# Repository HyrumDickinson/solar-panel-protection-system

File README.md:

# Solar Panel Protection System

## Project overview
This code represents the software portion of an ongoing effort to build a tool that monitors solar energy systems and keeps panels from overheating.

This project is funded by the University of Illinois Department of Electrical & Computer Engineering and is based out of the Center for Electric Machinery & Electromechanics. The project lies under the direction of Arijit Banerjee, Assistant Professor in ECE. The software portion of the project is undergoing construction by undergraduate student workers Hyrum Dickinson and Benjamin Olaivar, supervised by Kevin Colravy, Research Engineer at CEME. Only the software portion of the solar panel protection system project is hosted on this repo.

The original solar panel protection system was created by then-undergraduate students Dillon Vadgama, Douglas Lee, and Sachin Reddy for their fall 2019 senior design project. Dubbed "Smart Interface for ECEB Research Solar Panels," the project won the Texas Instruments Best Project Award. Now, researchers from the University of Illinois are attempting to improve on their prototype to create a robust, scalable tool that can monitor entire solar energy systems and reliably keep individual panels from overheating.

This branch is primarily focused on the development of the onboard arduino code. This code will encompass everything from ethernet communication to sensor data reading. The majority of work done in this branch will be done under the 'arduino_data' directory, the 'test' files. Files in this directory are organized using platformio, which allows for convenient access/storage of libraries, test code, and other files. 

## Repository setup
### `main`
The latest stable, deployable version of the code is stored in the `main` branch.
### `python-2-version` and `python-3-version`
Until code is fully ported to Python 3, these branches are the `main` branches of the code in their respective language.
### `original`
It is important to note that the original code for this project is not our own. It was written by Dillon Vadgama, Douglas Lee, and Sachin Reddy as part of a senior design project. The exact original code, including the original README, is stored in this branch. 

## System tools  
### Software  
Microprocessor code - Arduino Language  
Original GUI - Python 2 & Tkinter  
New GUI - Processing 3  
README & WRITEME files - Markdown  
### Hardware (not included in repo)  
Arduino Uno with Wifi  
Custom PCB Arduino Shield  

## Old Python GUI
### Dependencies
- matplotlib  
- tkinter (Python 3) or Tkinter (Python 2)  
- sqlite3  
- pillow  
- datetime  
The original code was written to for PIL. PIL is now unsupported - its own website recommends against its use. Pillow is a maintained backwords-compatible fork of PIL.
### Run
run Main.py in your preferred Python environment
### Building
source venv/bin/activate  
python2 Setup.py py2app -A

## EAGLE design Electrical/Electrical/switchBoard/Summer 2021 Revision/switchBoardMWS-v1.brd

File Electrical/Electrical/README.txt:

================================================================================================
GENERAL
================================================================================================

All PCB's were made using EAGLE 9.5.0
All PCB's were ordered through PCBWay.
Latest Gerber files were zipped and uploaded in each project folder.
For the BOM including parts to populate the PCB's, see the Documentation folder on Box.

================================================================================================
PCBWAY ORDER INFORMATION
================================================================================================

Gerber Files: smartInterface.zip
Board Type: Single Pieces
Different Design in Panel: 1
Size: 100 mm x 100 mm
Quantity: 10
Number of Layers: 4
Layer Stack:
 - L1: smartInterface.top
 - L2: smartInterface.ly2
 - L3: smartInterface.ly3
 - L4: smartInterface.bot
Material: FR-4
FR4-TG: TG 150-160
Thickness: 1.6
Min Track/Spacing: 6/6 mil
Min Hole Size: 0.3 mm
Solder Mask: Red
Silkscreen: White
Gold Fingers: No
Surface Finish: HASL with lead
Via Process: Tenting Vias
Finished Copper: 1 oz Cu
Inner Copper: 1 oz

Gerber Files: switchBoard.zip
Board Type: Single Pieces
Different Design in Panel: 1
Size: 25mm x 100mm
Quantity: 10
Number of Layers: 2
Layer Stack:
 - L1: switchBoard.top
 - L2: switchBoard.bot
Material: FR-4
FR4-TG: TG 150-160
Thickness: 1.6
Min Track/Spacing: 6/6 mil
Min Hole Size: 0.3 mm
Solder Mask: Red
Silkscreen: White
Gold Fingers: No
Surface Finish: HASL with lead
Via Process: Tenting Vias
Finished Copper: 1 oz Cu
Inner Copper: 1 oz

================================================================================================
BURNING THE BOOTLOADER - DO THIS BEFORE MOUNTING THE ATMEGA328P ON THE PCB
================================================================================================
To use the firmware that was originally written for the system, the Arduino bootloader should be burned onto the ATmega328P.

Here are resources to burn the bootloader:
https://www.arduino.cc/en/Tutorial/ArduinoToBreadboard
https://www.arduino.cc/en/Main/Standalone

================================================================================================
FLASHING FIRMWARE
================================================================================================
After burning the bootloader into the ATmega328P, the chip can be placed on the PCB.
The PCB was designed so that the microcontroller could be programmed without removing the chip.
Near the Ethernet connector is a 6 pin header that is used for programming.

The system was designed to be flashed with an FTDI Basic Breakout board from Sparkfun Electronics:
https://www.sparkfun.com/products/9716

Connect this FTDI board to the 6 pin header, and connector a USB cable from the FTDI board to your computer.
You can then use the Arduino IDE to flash any desired Arduino firmware to the system.

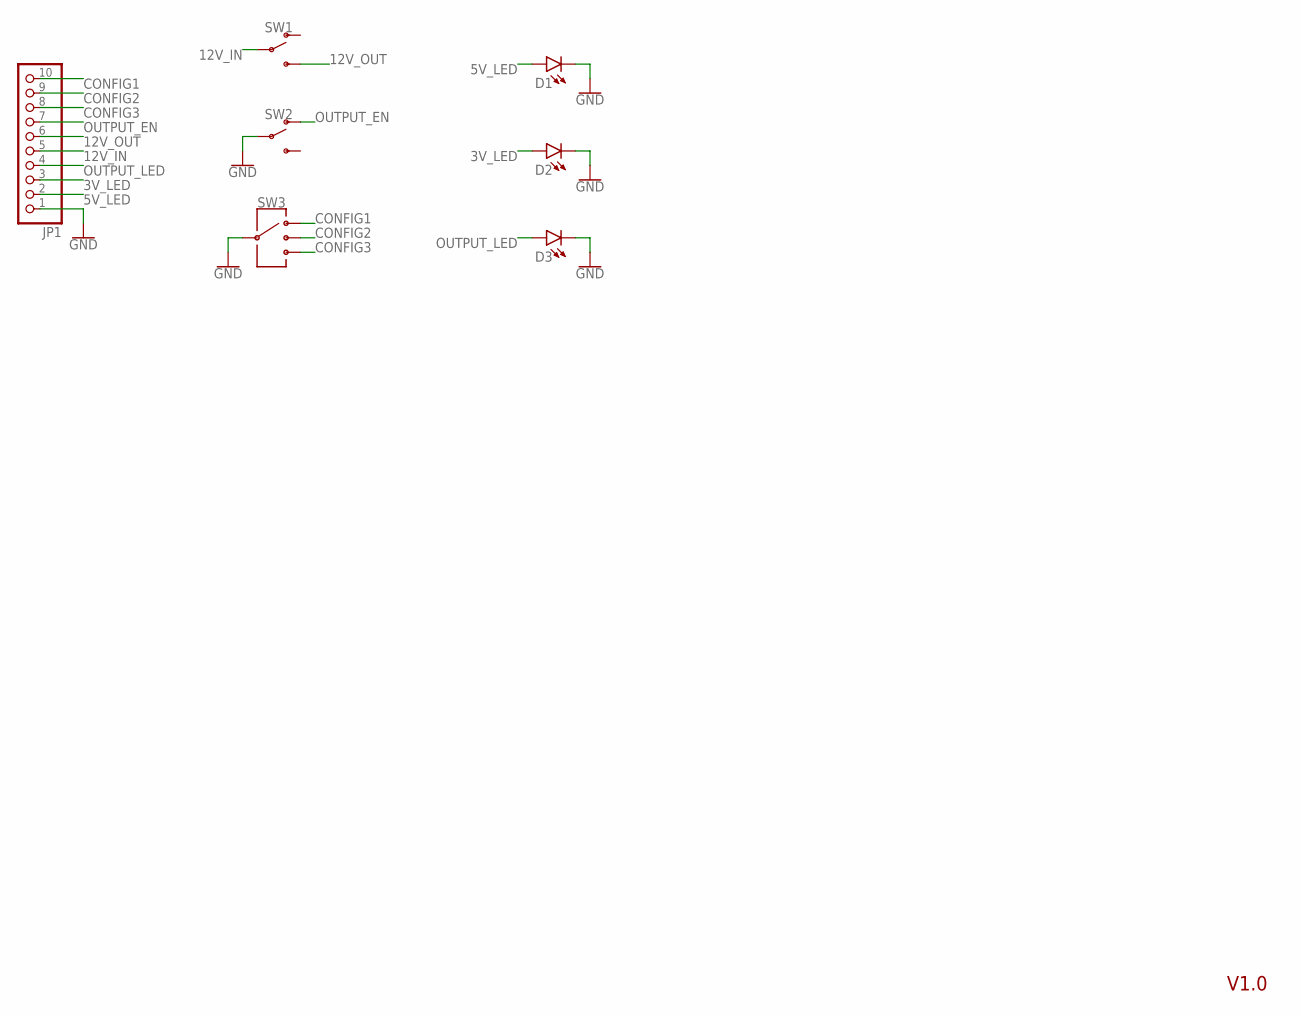
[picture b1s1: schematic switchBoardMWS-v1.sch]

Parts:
D1, D2, D3: LED5MM; LED_5MM
JP1: PINHD-1X10; 1X10
SW1, SW2: SPDT
SW3: SP3T

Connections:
3V_LED: D2.A, JP1.3
5V_LED: D1.A, JP1.2
12V_IN: JP1.5, SW1.2
12V_OUT: JP1.6, SW1.3 (S)
CONFIG1: JP1.10, SW3.P$1 (1)
CONFIG2: JP1.9, SW3.P$3 (3)
CONFIG3: JP1.8, SW3.P$4 (4)
GND: D1.K (C), D2.K (C), D3.K (C), JP1.1, SW2.2, SW3.P$2 (2)
OUTPUT_EN: JP1.7, SW2.1 (O)
OUTPUT_LED: D3.A, JP1.4

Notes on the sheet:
V1.0

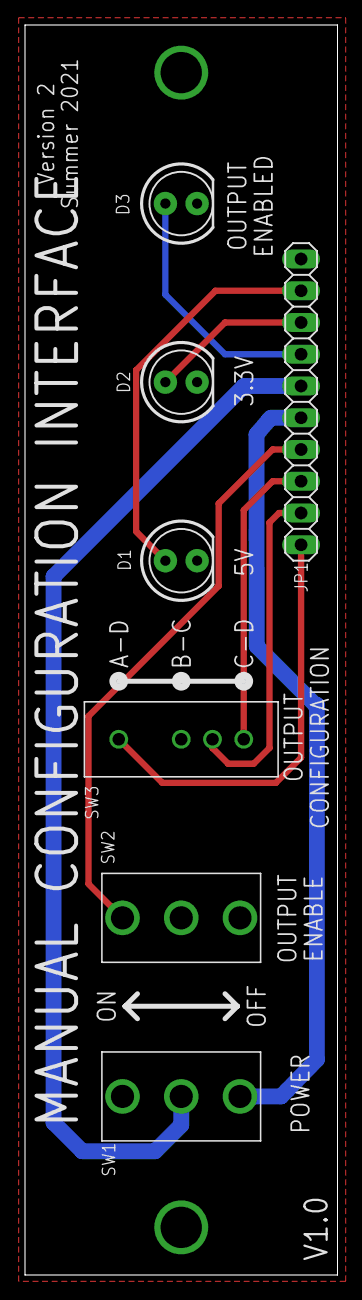
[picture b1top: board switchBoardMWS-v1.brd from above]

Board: 2 copper layers, 25.0 x 100.0 mm, 7 parts (0 on the bottom side), 10 nets.

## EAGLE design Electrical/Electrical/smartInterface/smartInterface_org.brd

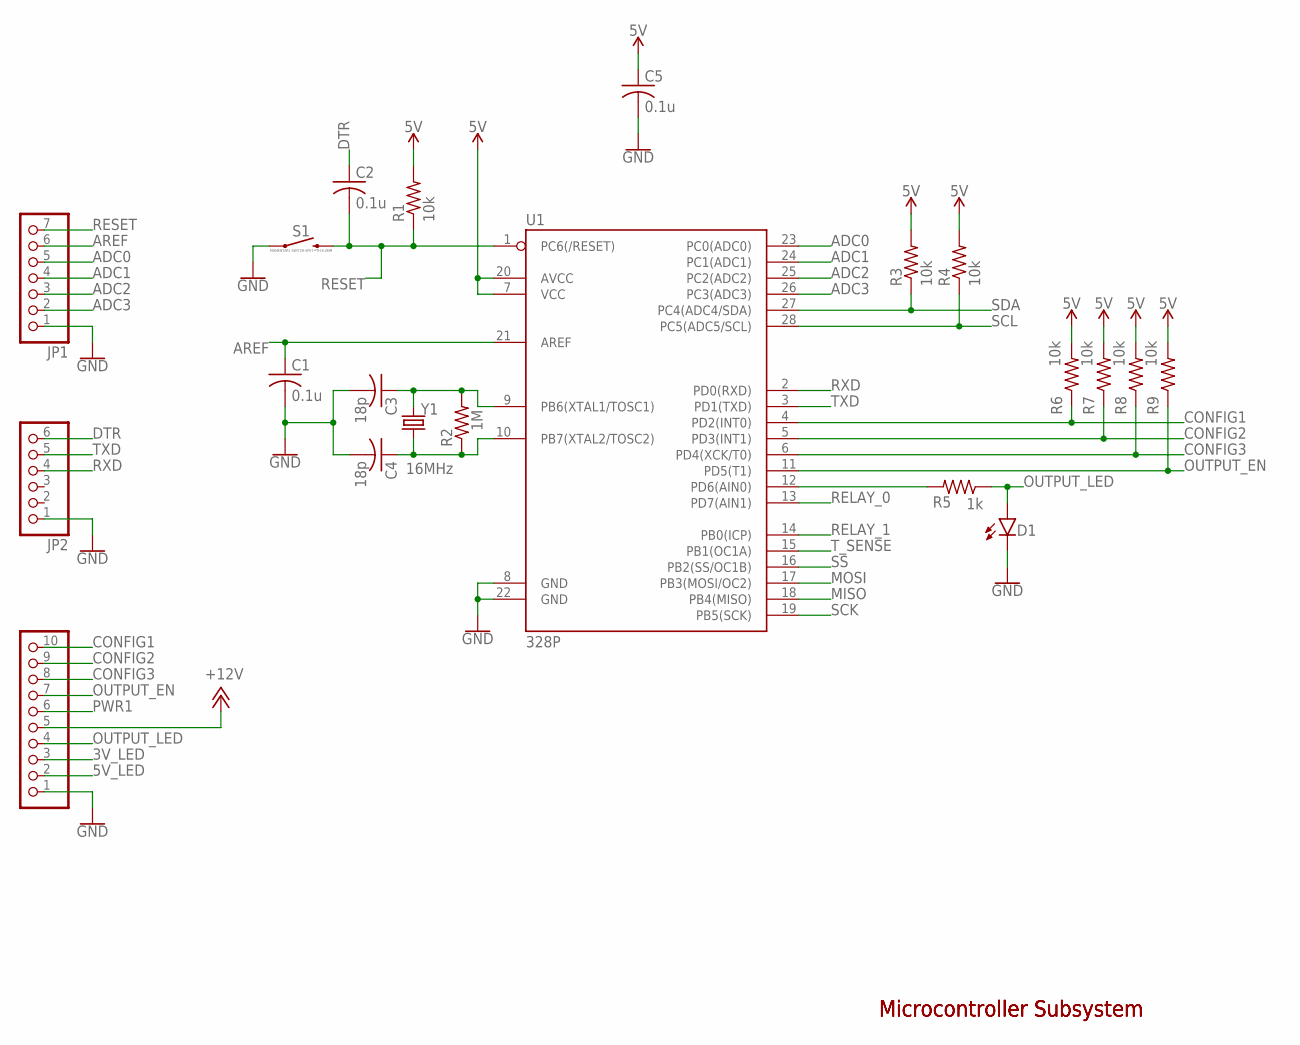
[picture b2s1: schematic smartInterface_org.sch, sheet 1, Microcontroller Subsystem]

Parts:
C1, C2, C5: 0.1u; C0603
C3, C4: 18p; C0603
D1: LED0603; LED-0603
JP1: PINHD-1X7; 1X07
JP2: PINHD-1X6/90; 1X06/90
JP5: PINHD-1X10; 1X10
R1, R3, R4, R6, R7, R8, R9: 10k; R0603
R2: 1M; R0603
R5: 1k; R0603
S1: MOMENTARY-SWITCH-SPST-PTH-6.0MM; TACTILE_SWITCH_PTH_6.0MM
U1: 328P; DIP28
Y1: 16MHz; HC49US

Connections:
3V_LED: JP5.3; also elsewhere on the board
5V: C5.1, R1.2, R3.2, R4.2, R6.2, R7.2, R8.2, R9.2, U1.7 (VCC), U1.20 (AVCC); also elsewhere on the board
5V_LED: JP5.2; also elsewhere on the board
+12V: JP5.5; also elsewhere on the board
ADC0: JP1.5, U1.23 (PC0(ADC0))
ADC1: JP1.4, U1.24 (PC1(ADC1))
ADC2: JP1.3, U1.25 (PC2(ADC2))
ADC3: JP1.2, U1.26 (PC3(ADC3))
AREF: C1.1, JP1.6, U1.21 (AREF)
CONFIG1: JP5.10, R6.1, U1.4 (PD2(INT0))
CONFIG2: JP5.9, R7.1, U1.5 (PD3(INT1))
CONFIG3: JP5.8, R8.1, U1.6 (PD4(XCK/T0))
DTR: C2.1, JP2.6
GND: C1.2, C3.2, C4.2, C5.2, D1.C, JP1.1, JP2.1, JP5.1, S1.1, U1.8 (GND), U1.22 (GND); also elsewhere on the board
MISO: U1.18 (PB4(MISO)); also elsewhere on the board
MOSI: U1.17 (PB3(MOSI/OC2)); also elsewhere on the board
unnamed: C3.1, R2.2, U1.9 (PB6(XTAL1/TOSC1)), Y1.2
unnamed: C4.1, R2.1, U1.10 (PB7(XTAL2/TOSC2)), Y1.1
unnamed: R5.2, U1.12 (PD6(AIN0))
OUTPUT_EN: JP5.7, R9.1, U1.11 (PD5(T1))
OUTPUT_LED: D1.A, JP5.4, R5.1
PWR1: JP5.6; also elsewhere on the board
RELAY_0: U1.13 (PD7(AIN1)); also elsewhere on the board
RELAY_1: U1.14 (PB0(ICP)); also elsewhere on the board
RESET: C2.2, JP1.7, R1.1, S1.3 (2), U1.1 (PC6(/RESET)); also elsewhere on the board
RXD: JP2.4, U1.2 (PD0(RXD))
SCK: U1.19 (PB5(SCK)); also elsewhere on the board
SCL: R4.1, U1.28 (PC5(ADC5/SCL)); also elsewhere on the board
SDA: R3.1, U1.27 (PC4(ADC4/SDA)); also elsewhere on the board
SS: U1.16 (PB2(SS/OC1B)); also elsewhere on the board
TXD: JP2.5, U1.3 (PD1(TXD))
T_SENSE: U1.15 (PB1(OC1A)); also elsewhere on the board

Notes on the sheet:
Microcontroller Subsystem

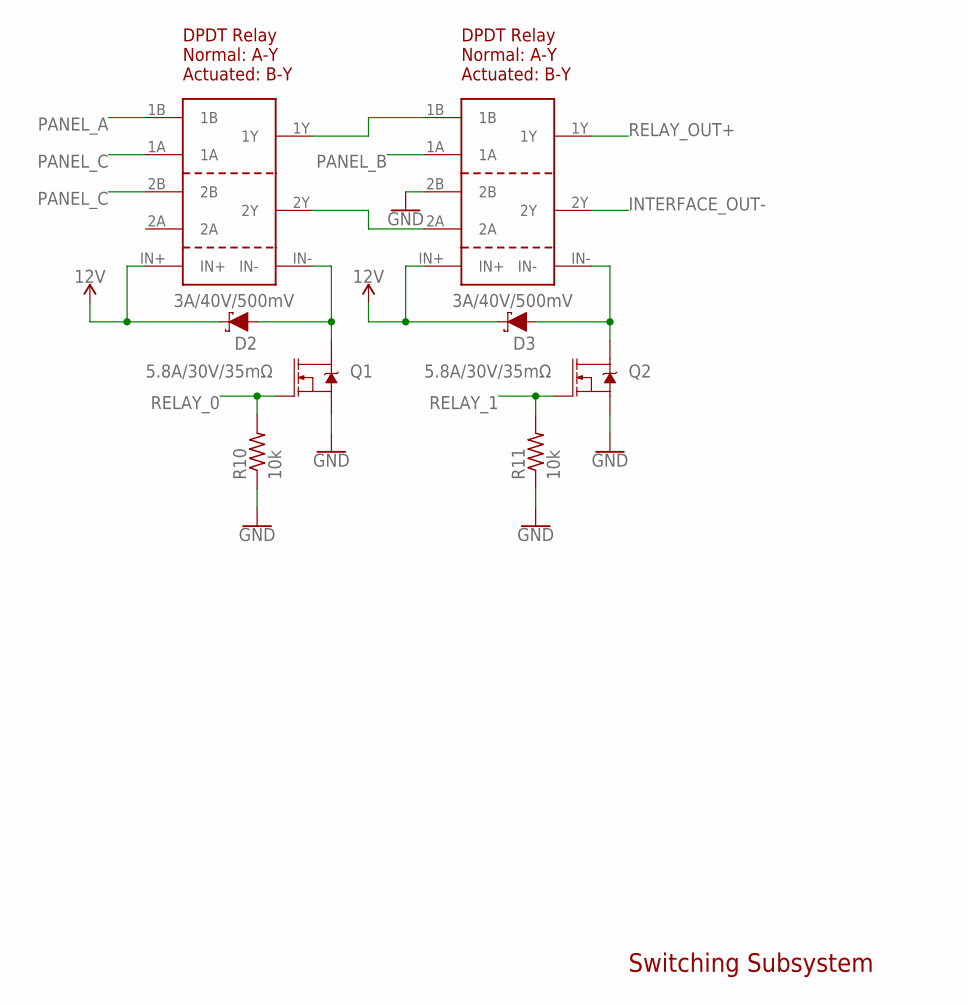
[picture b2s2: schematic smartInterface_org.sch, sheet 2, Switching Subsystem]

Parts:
D2, D3: 3A/40V/500mV; SMA-DIODE
K1, K2: DPDT_RELAY
Q1, Q2: 5.8A/30V/35mΩ; SOT23-3
R10, R11: 10k; R0603

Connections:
12V: D2.C, D3.C, K1.IN+, K2.IN+; also elsewhere on the board
GND: K2.2B, Q1.2 (S), Q2.2 (S), R10.1, R11.1; also elsewhere on the board
INTERFACE_OUT-: K2.2Y; also elsewhere on the board
unnamed: K1.1Y, K2.1B
unnamed: K1.2Y, K2.2A
unnamed: D2.A, K1.IN-, Q1.3 (D)
unnamed: D3.A, K2.IN-, Q2.3 (D)
PANEL_A: K1.1B; also elsewhere on the board
PANEL_B: K2.1A; also elsewhere on the board
PANEL_C: K1.1A, K1.2B; also elsewhere on the board
RELAY_0: Q1.1 (G), R10.2; also elsewhere on the board
RELAY_1: Q2.1 (G), R11.2; also elsewhere on the board
RELAY_OUT+: K2.1Y; also elsewhere on the board

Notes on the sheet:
Switching Subsystem
DPDT Relay Normal: A-Y Actuated: B-Y

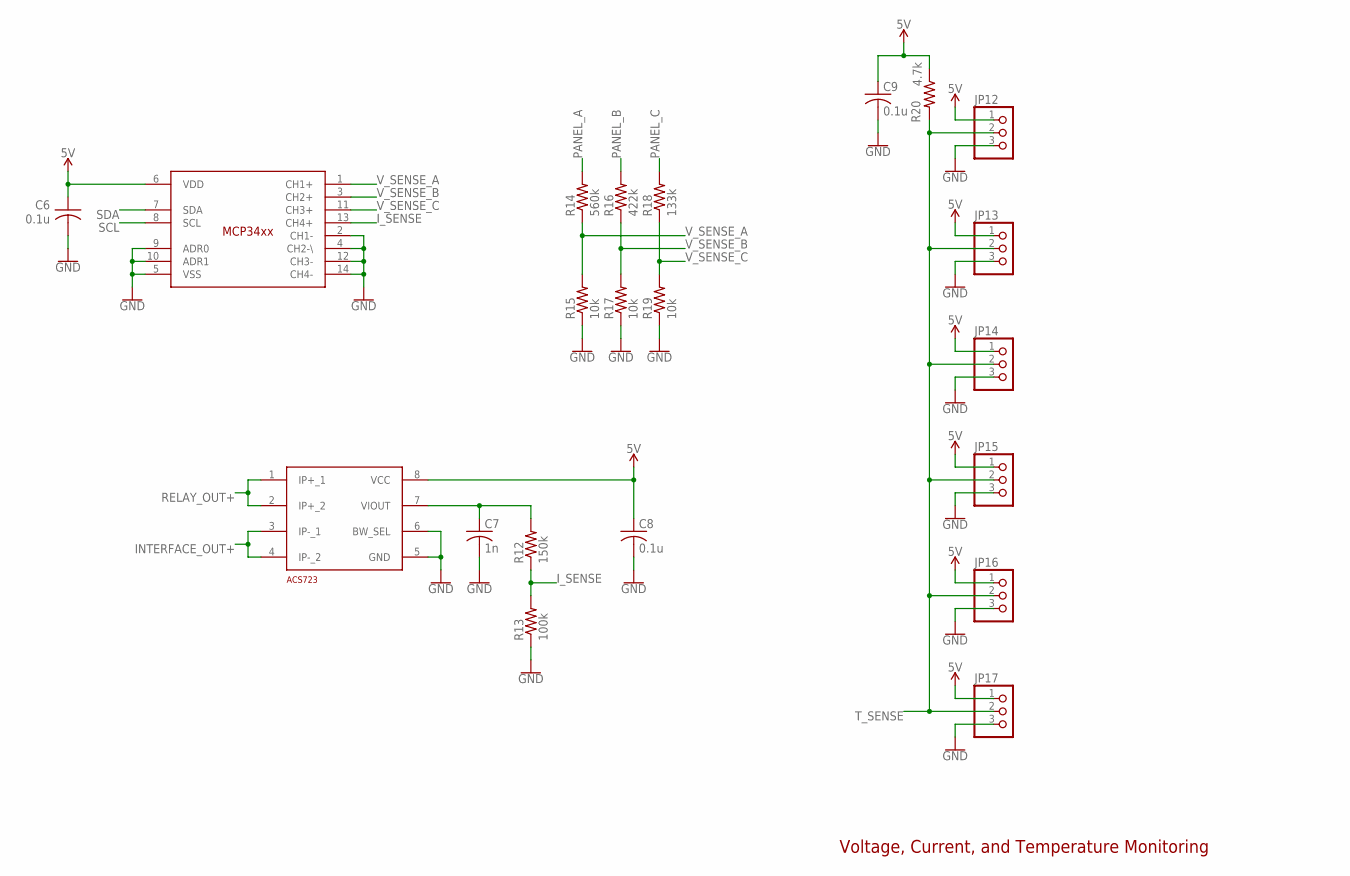
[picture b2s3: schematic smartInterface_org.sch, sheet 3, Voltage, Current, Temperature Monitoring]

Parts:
C6, C8: 0.1u; C0603
C7: 1n; C0603
C9: 0.1u; C0805
JP12, JP13, JP14, JP15, JP16, JP17: PINHD-1X3; 1X03
R12: 150k; R0603
R13: 100k; R0603
R14: 560k; R0603
R15, R17, R19: 10k; R0603
R16: 422k; R0603
R18: 133k; R0603
R20: 4.7k; R0603
U2: MCP3428; SO14
U3: ACS723; SO08

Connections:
5V: C6.1, C8.1, C9.1, JP12.1, JP13.1, JP14.1, JP15.1, JP16.1, JP17.1, R20.1, U2.6 (VDD), U3.8 (VCC); also elsewhere on the board
GND: C6.2, C7.2, C8.2, C9.2, JP12.3, JP13.3, JP14.3, JP15.3, JP16.3, JP17.3, R13.1, R15.1, R17.1, R19.1, U2.2 (CH1-), U2.4 (CH2-\), U2.5 (VSS), U2.9 (ADR0), U2.10 (ADR1), U2.12 (CH3-), U2.14 (CH4-), U3.5 (GND), U3.6 (BW_SEL); also elsewhere on the board
INTERFACE_OUT+: U3.3 (IP-_1), U3.4 (IP-_2); also elsewhere on the board
I_SENSE: R12.1, R13.2, U2.13 (CH4+)
unnamed: C7.1, R12.2, U3.7 (VIOUT)
PANEL_A: R14.2; also elsewhere on the board
PANEL_B: R16.2; also elsewhere on the board
PANEL_C: R18.2; also elsewhere on the board
RELAY_OUT+: U3.1 (IP+_1), U3.2 (IP+_2); also elsewhere on the board
SCL: U2.8 (SCL); also elsewhere on the board
SDA: U2.7 (SDA); also elsewhere on the board
T_SENSE: JP12.2, JP13.2, JP14.2, JP15.2, JP16.2, JP17.2, R20.2; also elsewhere on the board
V_SENSE_A: R14.1, R15.2, U2.1 (CH1+)
V_SENSE_B: R16.1, R17.2, U2.3 (CH2+)
V_SENSE_C: R18.1, R19.2, U2.11 (CH3+)

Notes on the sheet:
Voltage, Current, and Temperature Monitoring

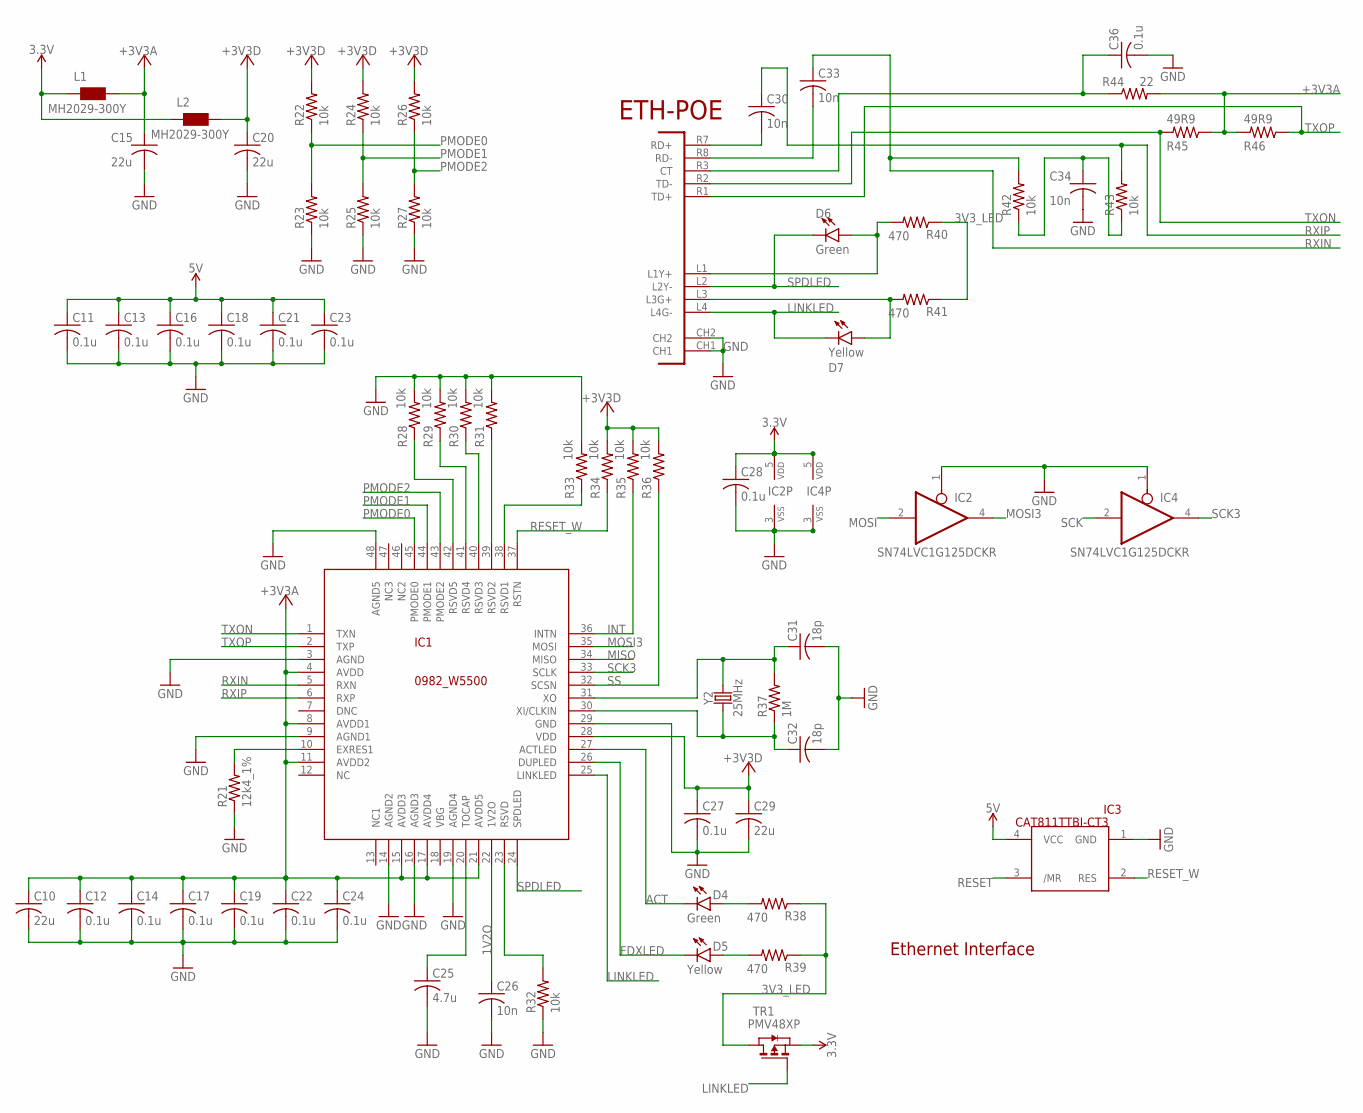
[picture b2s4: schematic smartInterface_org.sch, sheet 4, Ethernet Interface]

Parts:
C10, C15, C20, C29: 22u; C0603
C11, C12, C13, C14, C16, C17, C18, C19, C21, C22, C23, C24, C27, C28, C36: 0.1u; C0603
C25: 4.7u; C0603
C26, C30, C33, C34: 10n; C0603
C31, C32: 18p; C0603
D4, D6: Green; LED-0603
D5, D7: Yellow; LED-0603
ETH1: RB1-125BHQ1A; POE-RJ45
IC1: 0982_W5500; TQFP48-7X7
IC2, IC4: SN74LVC1G125DCKR; SC70-5
IC3: CAT811TTBI-CT3; SOT143
L1, L2: MH2029-300Y; 0805
R21: 12k4_1%; R0603
R22, R23, R24, R25, R26, R27, R28, R29, R30, R31, R32, R33, R34, R35, R36, R42, R43: 10k; R0603
R37: 1M; R0603
R38, R39, R40, R41: 470; R0603
R44: 22; R0603
R45, R46: 49R9; R0603
TR1: PMV48XP; SOT-23; PART_NUMBER PMV48XP
Y2: 25MHz; HC49US

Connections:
1V2O: C26.1, IC1.22 (1V2O)
3.3V: C28.1, IC2.5 (VDD), IC4.5 (VDD), L1.1, L2.1, TR1.2 (S); also elsewhere on the board
3V3_LED: R38.1, R39.1, R40.1, R41.1, TR1.1 (D)
5V: C11.1, C13.1, C16.1, C18.1, C21.1, C23.1, IC3.4 (VCC); also elsewhere on the board
+3V3A: C10.1, C12.1, C14.1, C15.1, C17.1, C19.1, C22.1, C24.1, IC1.4 (AVDD), IC1.8 (AVDD1), IC1.11 (AVDD2), IC1.15 (AVDD3), IC1.17 (AVDD4), IC1.21 (AVDD5), L1.2, R44.2, R45.1, R46.2
+3V3D: C20.1, C27.1, C29.1, IC1.28 (VDD), L2.2, R22.2, R24.2, R26.2, R34.2, R35.2, R36.2
ACT: D4.C, IC1.27 (ACTLED)
FDXLED: D5.C, IC1.26 (DUPLED)
GND: C10.2, C11.2, C12.2, C13.2, C14.2, C15.2, C16.2, C17.2, C18.2, C19.2, C20.2, C21.2, C22.2, C23.2, C24.2, C25.2, C26.2, C27.2, C28.2, C29.2, C31.2, C32.2, C34.2, C36.2, ETH1.CH1, ETH1.CH2, IC1.3 (AGND), IC1.9 (AGND1), IC1.14 (AGND2), IC1.16 (AGND3), IC1.19 (AGND4), IC1.29 (GND), IC1.48 (AGND5), IC2.1 (OE), IC2.3 (VSS), IC3.1 (GND), IC4.1 (OE), IC4.3 (VSS), R21.1, R23.1, R25.1, R27.1, R28.2, R29.2, R30.2, R31.2, R32.1, R33.2; also elsewhere on the board
INT: IC1.36 (INTN), R35.1
LINKLED: D7.C, ETH1.L4 (L4G-), IC1.25 (LINKLED), TR1.3 (G)
MISO: IC1.34 (MISO); also elsewhere on the board
MOSI: IC2.2 (I); also elsewhere on the board
MOSI3: IC1.35 (MOSI), IC2.4 (O)
unnamed: C31.1, IC1.31 (XO), R37.2, Y2.2
unnamed: IC1.39 (RSVD2), R31.1
unnamed: D4.A, R38.2
unnamed: IC1.23 (RSVD), R32.2
unnamed: D7.A, ETH1.L3 (L3G+), R41.2
unnamed: D6.A, ETH1.L1 (L1Y+), R40.2
unnamed: C34.1, R42.1, R43.1
unnamed: C30.2, ETH1.R7 (RD+)
unnamed: C33.2, ETH1.R8 (RD-)
unnamed: D5.A, R39.2
unnamed: IC1.40 (RSVD3), R30.1
unnamed: IC1.41 (RSVD4), R29.1
unnamed: C36.1, ETH1.R3 (CT), R44.1
unnamed: IC1.42 (RSVD5), R28.1
unnamed: C25.1, IC1.20 (TOCAP)
unnamed: IC1.38 (RSVD1), R33.1
unnamed: IC1.10 (EXRES1), R21.2
NC: IC1.12 (NC)
OSC2E2: C32.1, IC1.30 (XI/CLKIN), R37.1, Y2.1
PMODE0: IC1.45 (PMODE0), R22.1, R23.2
PMODE1: IC1.44 (PMODE1), R24.1, R25.2
PMODE2: IC1.43 (PMODE2), R26.1, R27.2
RESET: IC3.3 (/MR); also elsewhere on the board
RESET_W: IC1.37 (RSTN), IC3.2 (RES), R34.1
RXIN: C33.1, IC1.5 (RXN), R42.2
RXIP: C30.1, IC1.6 (RXP), R43.2
SCK: IC4.2 (I); also elsewhere on the board
SCK3: IC1.33 (SCLK), IC4.4 (O)
SPDLED: D6.C, ETH1.L2 (L2Y-), IC1.24 (SPDLED)
SS: IC1.32 (SCSN), R36.1; also elsewhere on the board
TXON: ETH1.R2 (TD-), IC1.1 (TXN), R45.2
TXOP: ETH1.R1 (TD+), IC1.2 (TXP), R46.1

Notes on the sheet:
Ethernet Interface
ETH-POE

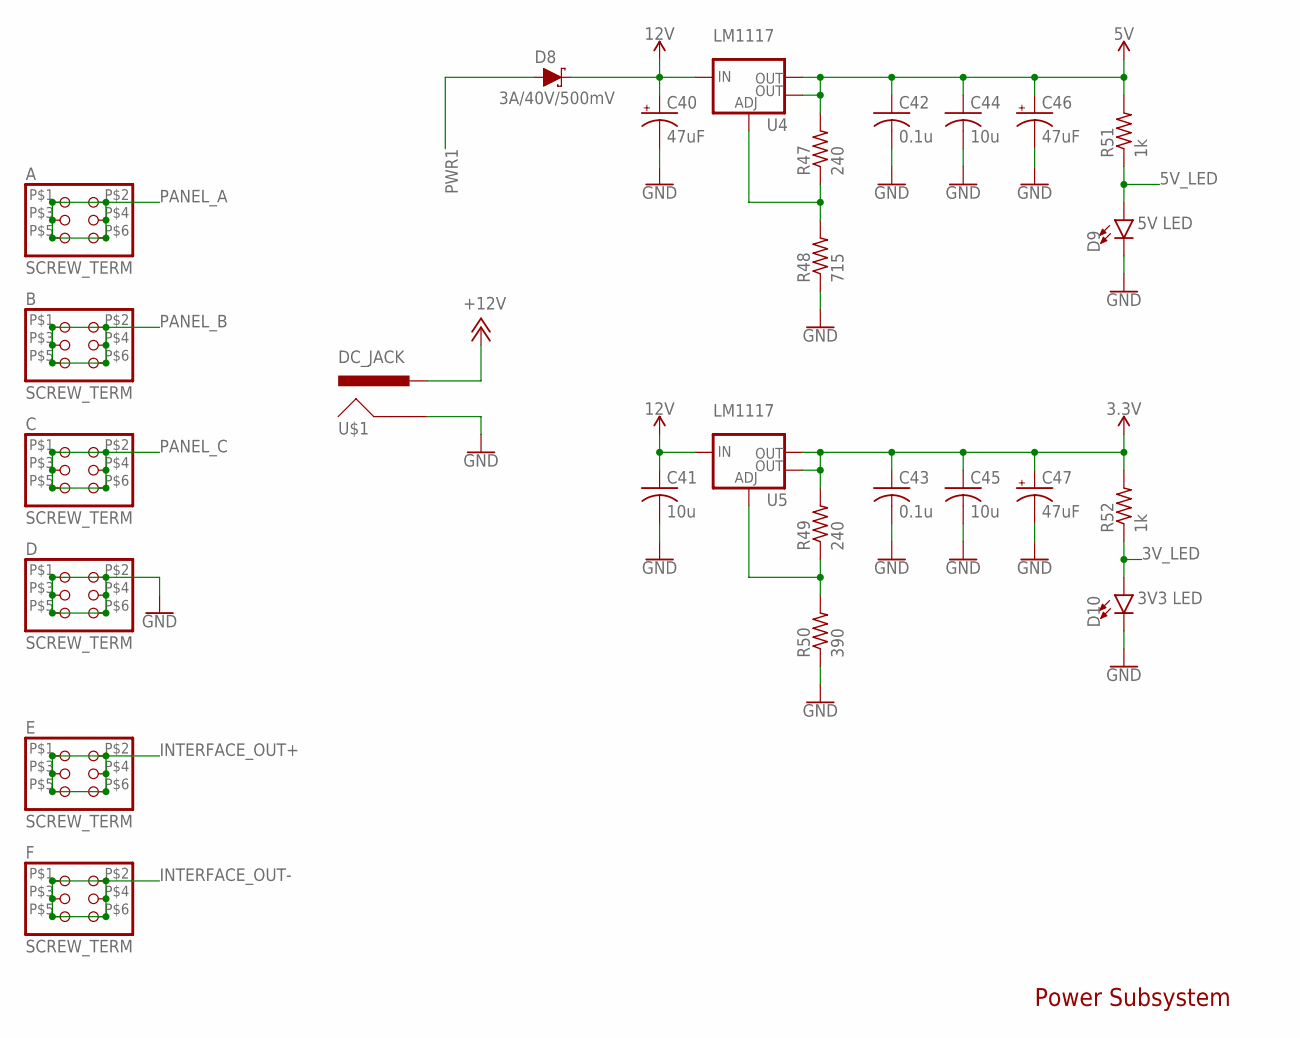
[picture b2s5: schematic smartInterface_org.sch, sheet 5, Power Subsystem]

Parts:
A: SCREW_TERM
B: SCREW_TERM
C: SCREW_TERM
C40, C46, C47: 47uF; PANASONIC_D
C41, C44, C45: 10u; C0805
C42, C43: 0.1u; C0603
D: SCREW_TERM
D8: 3A/40V/500mV; SMA-DIODE
D9: 5V LED; LED-0603
D10: 3V3 LED; LED-0603
E: SCREW_TERM
F: SCREW_TERM
R47, R49: 240; R0603
R48: 715; R0603
R50: 390; R0603
R51, R52: 1k; R0603
U4, U5: LM1117; SOT223
U$1: DC_JACK; POWER_JACK_PTH

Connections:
3.3V: C43.1, C45.1, C47.+, R49.2, R52.2, U5.2 (OUT), U5.4 (OUT); also elsewhere on the board
3V_LED: D10.A, R52.1; also elsewhere on the board
5V: C42.1, C44.1, C46.+, R47.2, R51.2, U4.2 (OUT), U4.4 (OUT); also elsewhere on the board
5V_LED: D9.A, R51.1; also elsewhere on the board
12V: C40.+, C41.1, D8.C, U4.3 (IN), U5.3 (IN); also elsewhere on the board
+12V: U$1.PWR; also elsewhere on the board
GND: C40.-, C41.2, C42.2, C43.2, C44.2, C45.2, C46.-, C47.-, D.P$1 (1), D.P$2 (2), D.P$3 (3), D.P$4 (4), D.P$5 (5), D.P$6 (6), D9.C, D10.C, R48.1, R50.1, U$1.GND; also elsewhere on the board
INTERFACE_OUT+: E.P$1 (1), E.P$2 (2), E.P$3 (3), E.P$4 (4), E.P$5 (5), E.P$6 (6); also elsewhere on the board
INTERFACE_OUT-: F.P$1 (1), F.P$2 (2), F.P$3 (3), F.P$4 (4), F.P$5 (5), F.P$6 (6); also elsewhere on the board
unnamed: R47.1, R48.2, U4.1 (ADJ)
unnamed: R49.1, R50.2, U5.1 (ADJ)
PANEL_A: A.P$1 (1), A.P$2 (2), A.P$3 (3), A.P$4 (4), A.P$5 (5), A.P$6 (6); also elsewhere on the board
PANEL_B: B.P$1 (1), B.P$2 (2), B.P$3 (3), B.P$4 (4), B.P$5 (5), B.P$6 (6); also elsewhere on the board
PANEL_C: C.P$1 (1), C.P$2 (2), C.P$3 (3), C.P$4 (4), C.P$5 (5), C.P$6 (6); also elsewhere on the board
PWR1: D8.A; also elsewhere on the board

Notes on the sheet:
Power Subsystem

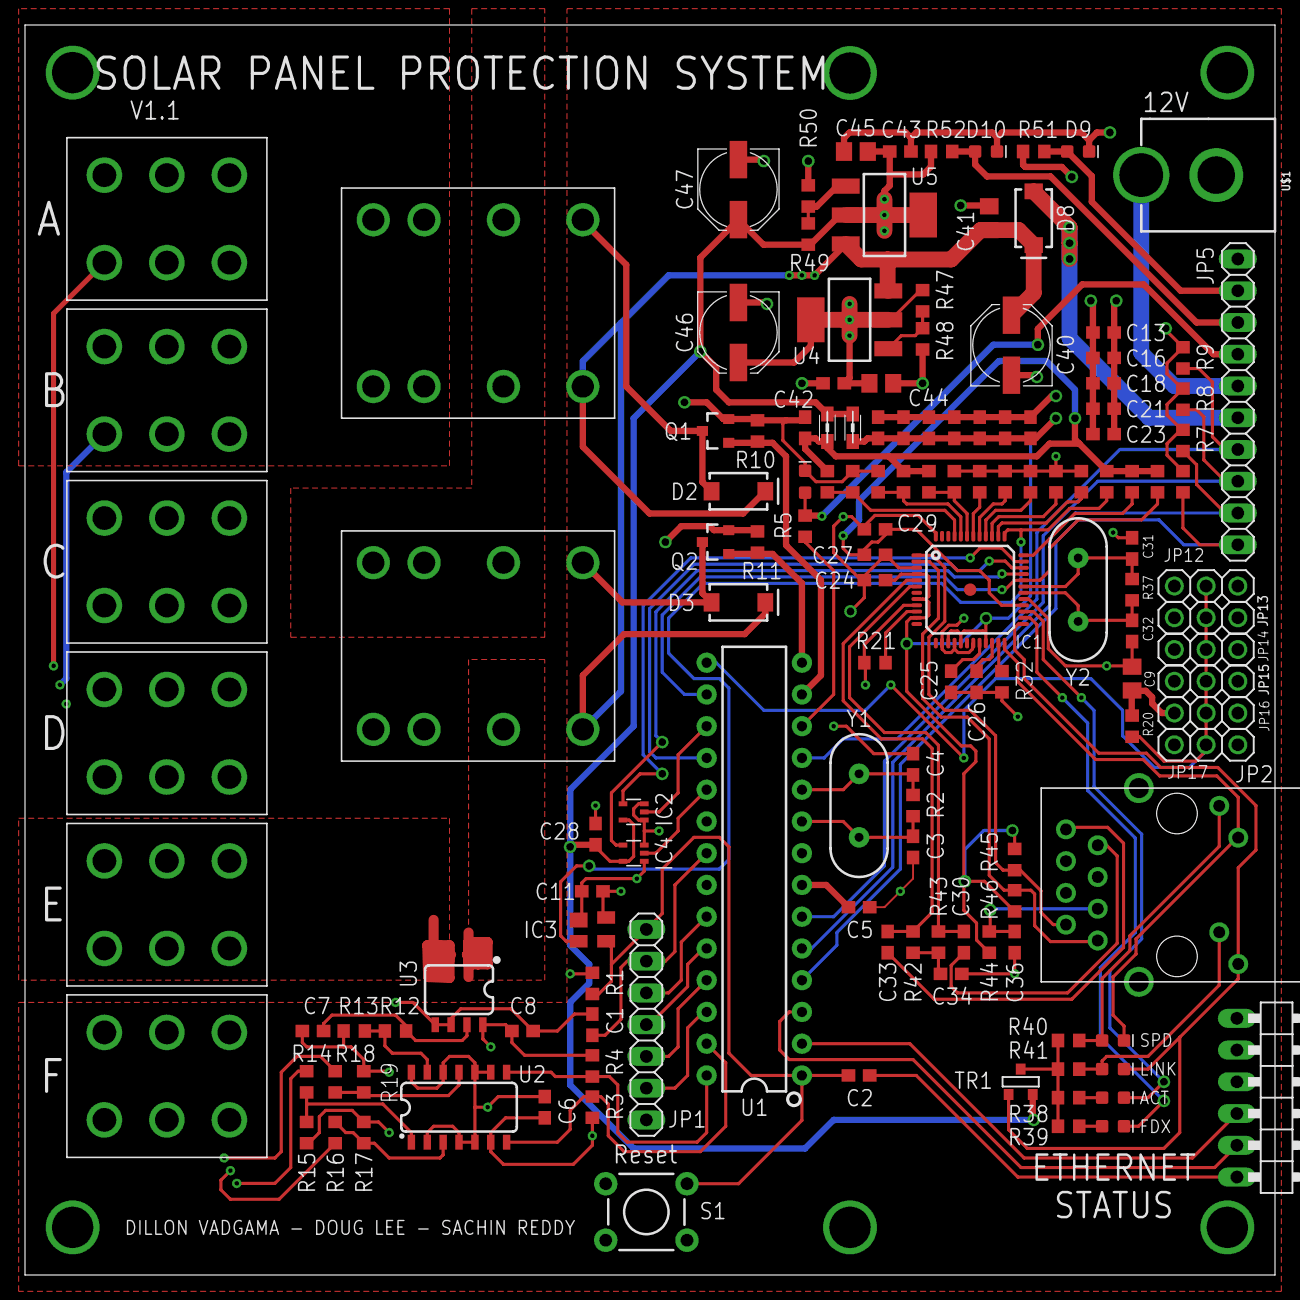
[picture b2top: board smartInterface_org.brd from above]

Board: 4 copper layers, 100.0 x 100.0 mm, 141 parts (0 on the bottom side), 88 nets.

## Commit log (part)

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2021-06-03 upload original files
2021-06-06 copied README from parallel repo
    I created a new GitHub repo (this one) to more efficiently import a very large number of files that, turns out, were in the original project. Now I'm copying some minor changes that I made to the cod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
2021-06-06 README update
    removed reference to now-defunct box-files repo
2021-06-07 update README
    Deleted stray reference to box-files and added attribution to original coder Sachin Reddy.
2021-06-07 minor layout change
    separated one paragraph into two
2021-06-07 minor wording change
    removed redundant reference to PIL
2021-06-07 minor wording change
    remove unnecessary formal language
2021-06-07 minor wording change
    edited for clarity
2021-06-07 minor wording change
    edit to add descriptiveness
2021-06-07 minor wording change
    removed wordiness
2021-06-07 minor wording change
    edited for readability
2021-06-07 Created file and made initial logs
2021-06-07 minor heading edit
    added a note for Ben
2021-06-07 minor header edit
    edited note for Ben
2021-06-07 edit header
    edit note for Ben
2021-06-08 added arduino_dev branch and arduino_data files
2021-06-08 DHCP_test is success :) changes added to main.cpp
2021-06-11 changed imports to align with python 2 package names
2021-06-11 change imports statements to align with python 2 package names
2021-06-11 fix syntax error
    wrap paranthesis around argument in print statement
2021-06-11 fix syntax error
    wrap argument of print statement in paranthesis
2021-06-11 capitalize name of file
    import statements that reference this file reference a capitalized "Monitor" file rather than a lowercase "monitor" file. additionally, capitalizing the file name brings this project into compliance 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
2021-06-11 update reflecting fact that code now runs
    additionally, I provide instructions on how to run the code
2021-06-11 rename file to fix import error
    import statements captialize this file, and this file should be capitalized too. That's convention, after all
2021-06-11 copycat of python-2-version branch
2021-06-11 comment out tkk import
    it isnt needed
2021-06-11 add content
    add sentences reflecting the fact that the python-2-version is now up and running, but the python-3-version remains slow
2021-06-14 changed readPin
    changed readPin from A10 to A0 because Arduino Uno Wifi Rev 2 (the new board that we're testing) likes it better.
2021-06-14 edits for clarity
2021-06-14 fixed markdown error
2021-06-14 edited for clarity
2021-06-14 improved appearence
2021-06-14 added content
2021-06-14 corrected error
2021-06-15 converted dhcp to be command-based
2021-06-15 simplified ip confirmation
2021-06-16 copied ben's logs from arduino_dev branch
    it will be easiest to keep track of what each other are up to if we keep our logs all on the same file -- let's have that file be the `main` branch WRITEME
2021-06-16 minor content modification
2021-06-16 minor edit
2021-06-16 changed python 2 references to python 3
2021-06-16 Revert "Delete Setup.py"
    This reverts commit 023aacb0a057b8651ef8fe312d525f7176f14422.
2021-06-16 minor edits
2021-06-17 changed some GUI labels
    Kevin requested these changes to improve GUI intuitiveness
2021-06-17 added wifi connection info
2021-06-17 added wifi connection instructions
    added guidence for connectingto WPA-Enterprise encrypted networks, such as IllinoisNet.
2021-06-17 Created ConnectToWPA2EnterpriseEncryptedWifiNetwork.ino
    this file facilitates connection to a WPA2 - Enterprise encypted wifi network
2021-06-17 added 6-17-2021 dev notes to WRITEME.md
2021-06-18 placeholder functions for voltage/currnet sensor
2021-06-18 made changes to WRITEME
2021-06-18 changes to README
2021-06-21 changed GUI layout
    Moved the 'max temperature' box to the right slightly, to line it up with the other 'max ------' boxes
2021-06-21 added threshold control commands
2021-06-21 changes to WRITEME
2021-06-22 improved GUI layout
    lifted graph to improve readability and remove issue where bottom labels on graph were cut off by the buttons at the bottom of the screen
2021-06-22 improved GUI layout
    made 'trip points' larger and better positioned
2021-06-22 improved GUI cosmetics
    re-aligned databox and connectionbox borders (I had previously pushed them out of alignment when I made room for the labels at the bottom of the graph a few commits ago)
2021-06-23 improved GUI cosmetics
    lined max label names up, their respective input boxes up, and the unit of measurement symbols up. improved on the last lineup commit
2021-06-23 improved GUI cosmetics
    italicized unit measurement symbols, per conventional practice
2021-06-23 updated WRITEME.md for 6-23-2021
2021-06-23 added comments to DefaultSettings.py
2021-06-23 renamed "SolarPanelMonitor.py" to "Main.py"
2021-06-23 renamed "DefaultSettings.py" to "Settings.py"
    All other files which reference this file were also updated
2021-06-23 Updated WRITEME.md for 6-22-2021
2021-06-23 removed redundant import statements
    several files were importing other files multiple times. not any more
2021-06-23 removed redundant library imports
    several files were importing the same library more than once.
    redundant imports were commented out,
    so they can be re-added later if necessary
    I also added extensive notes on which libraries each file import imported
    to another file, so we can avoid similar redundancy in
    the future. after cleaning out these import
2021-06-23 fixed another redundant import
2021-06-23 replaced "thresholds" with "trip points"
    made changes only where they would improve code readability.
    confirmed that the code is not broken
2021-06-23 Updated README.md for 6-23-2021
2021-06-23 improved GUI interactivity
    added feature that highlights buttons in green when you press them
2021-06-23 improved GUI interactivity
2021-06-23 fixed syntax issue
    changed comparison of chars using is to comparison of ints usign ==
2021-06-26 improved editability of GUI
    changed trip point input boxes to have the same highlighting format as all other interactive widgets. right now, that means their background is set to white, their highlight background is green, and 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
2021-06-26 added comments explaining the function of each color
    I'm thinking of changing the local color variable names from their corresponding colors to their corresponding functions. Whichever one I use for a name, the other should be a comment to the left to 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
2021-06-26 deleted .pyc files
    I accidently added these. I thought my .gitignore was supposed to ensure
    they weren't commited. hmmm
2021-06-26 updated WRITEME.md for 6-26-2021
2021-06-26 added .gitignore
    we don't need pesky compiled python files on our GitHub
2021-06-26 made all buttons except checkboxes white
    checkboxes will require more work to color synchronize. I'll do them
    later
2021-06-26 renamed local color variables
    renamed local color variables to reference function rather than hue. Additionally, I added comments to Settings.py where the hue of each color can be noted, along with an explanation of its function 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
2021-06-26 Updated WRITEME.md
2021-06-26 updated .gitignore
    added specific pesky .pyc files
2021-06-28 local multiple temp readings working
2021-06-28 successfully integrated ethernet to temp readers
2021-06-28 changes to WRITEME.md
2021-06-28 fixed WRITEME format
2021-06-29 converted to array system in readTemperatures function
2021-06-29 added temperature threshold logic
2021-06-30 made GUI display connection status even if disconnected
    there is still the issue of connection statuses piling on top of each
    other rather than deleting the old statuses
    I'll need to have Google to figure out how
    to solve that problem. I can't right now
    because I'm on a train in Switzerland and I don't
    exactly have internet lol
2021-07-01 added pcb files (TALK TO KEVIN ABOUT NEW DESIGN) - finished json temp implimentation
2021-07-01 addded json and temp changes to main.cpp
2021-07-02 updated .gitignore to delete venv files
2021-07-08 started transceiver code
2021-07-08 added conda deactivation
2021-07-09 edited color scheme
2021-07-11 added powershell script for easier navigation
2021-07-15 successfully got transceiver baseplate code working
2021-07-22 change_node transceiver code working
2021-07-22 added detailed comments
2021-07-22 removed old code
2021-07-22 made all text same color
2021-07-22 graph text stays same color after updating
2021-07-22 added ethernet to main transceiver
2021-07-22 all buttons retain text color while being clicked
2021-07-22 renamed GRAPH_BACKGROUND_COLOR
2021-07-23 final GUI look (except graph & checkboxes)
    [X] Make all text, including all active text, colored by same local variable
    [X] Isolate graph background color from other local variables
    [X] Make all entire widget backgrounds colored by same local variable
    [X] Updated color named to reflect their new purposes
    [X] Create space between bottom buttons and bottom of widget
    [X] Make space between buttons and edge of widget same for all edge buttons
2021-07-23 updated WRITEME.md
    it's been awhile since I've updated this file. that is likely because I've been on vacation a lot, and dealing with Windows issues instead of coding at work. I hope I didn't forget to log an importan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
2021-07-23 added comment
2021-07-23 script to set up gui on new computer
2021-07-23 script to set up application on new computer
2021-07-23 larger area highlights when checkboxes are clicked
2021-07-23 graph is aesthetically pleasing
2021-07-23 added hex suggestions for alternate color themes
2021-07-23 updated WRITEME.md - gui look and feel complete
2021-07-26 made changes to README.txt
2021-07-26 organized test file and added command booleans on node and main boxes
2021-07-26 trying to connect arduino to GUI
2021-07-27 changed GUI theme
2021-07-27 deleted redundant file
2021-07-27 deleted .pyc files
2021-07-27 fixed merge error
2021-07-27 Revert "deleted redundant file"
    This reverts commit 0208b499e688981315b76714c7e6c7c924a9b420.
2021-07-27 fixed merge errors
2021-07-27 fixed last merge error
2021-07-27 Rename monitor.py to Monitor.py
2021-07-28 see full commit message for explanation
    Previously, the application was designed to connect directly to each solar panel's arduino. Each panel's arduino would send in its own unique data. the application would scan for the ip addresses of 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
2021-07-28 edits for code readability
2021-07-28 fixed error where checkbox interactions created pileup of connection statuses
2021-07-29 updated writeme
2021-07-29 edits to make python application only connect to one device
2021-07-30 added node identifier to JSON
2021-08-02 added processing frontend code
2021-08-02 adding main dev file for arduino processing code and renamed processing_arduino to processing_test
2021-08-02 renamed from .cpp to .ino file so Arduino IDE will open it
2021-08-02 changed COM #
2021-08-02 abandoned python GUI
2021-08-02 added button
2021-08-02 adjusted JSON to account for failed connections
2021-08-02 added ben_reference for processing frontend
2021-08-02 json successfully parses
2021-08-03 implemented controlP5 buttons on bens working area
2021-08-03 added node buttons. Currently pretty sloppy
2021-08-05 reorganized folders for easy opening in Processing
2021-08-05 added method to store node data in an array
2021-08-06 added shutdown command to frontend
2021-08-06 started building serious new GUI
2021-08-07 simplified button and tab events
2021-08-10 added color updates to buttons when updated
2021-08-10 improved documentation in presentation code
2021-08-10 optimized switching tabs/updating display
2021-08-11 added buttons/addons to settings tab
2021-08-11 created confirmChanges and restoreDefault buttons on settings page
2021-08-11 cleaned up code/comments for setup functions
2021-08-11 adding threshold commands on arduino nodes. Not working
2021-08-15 debugged commands for threshold changes. Changes now working

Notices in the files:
parts and their libraries:
SparkFun-IC-Microcontroller: Licensing: Creative Commons ShareAlike 4.0 International - https://creativecommons.org/licenses/by-sa/4.0
